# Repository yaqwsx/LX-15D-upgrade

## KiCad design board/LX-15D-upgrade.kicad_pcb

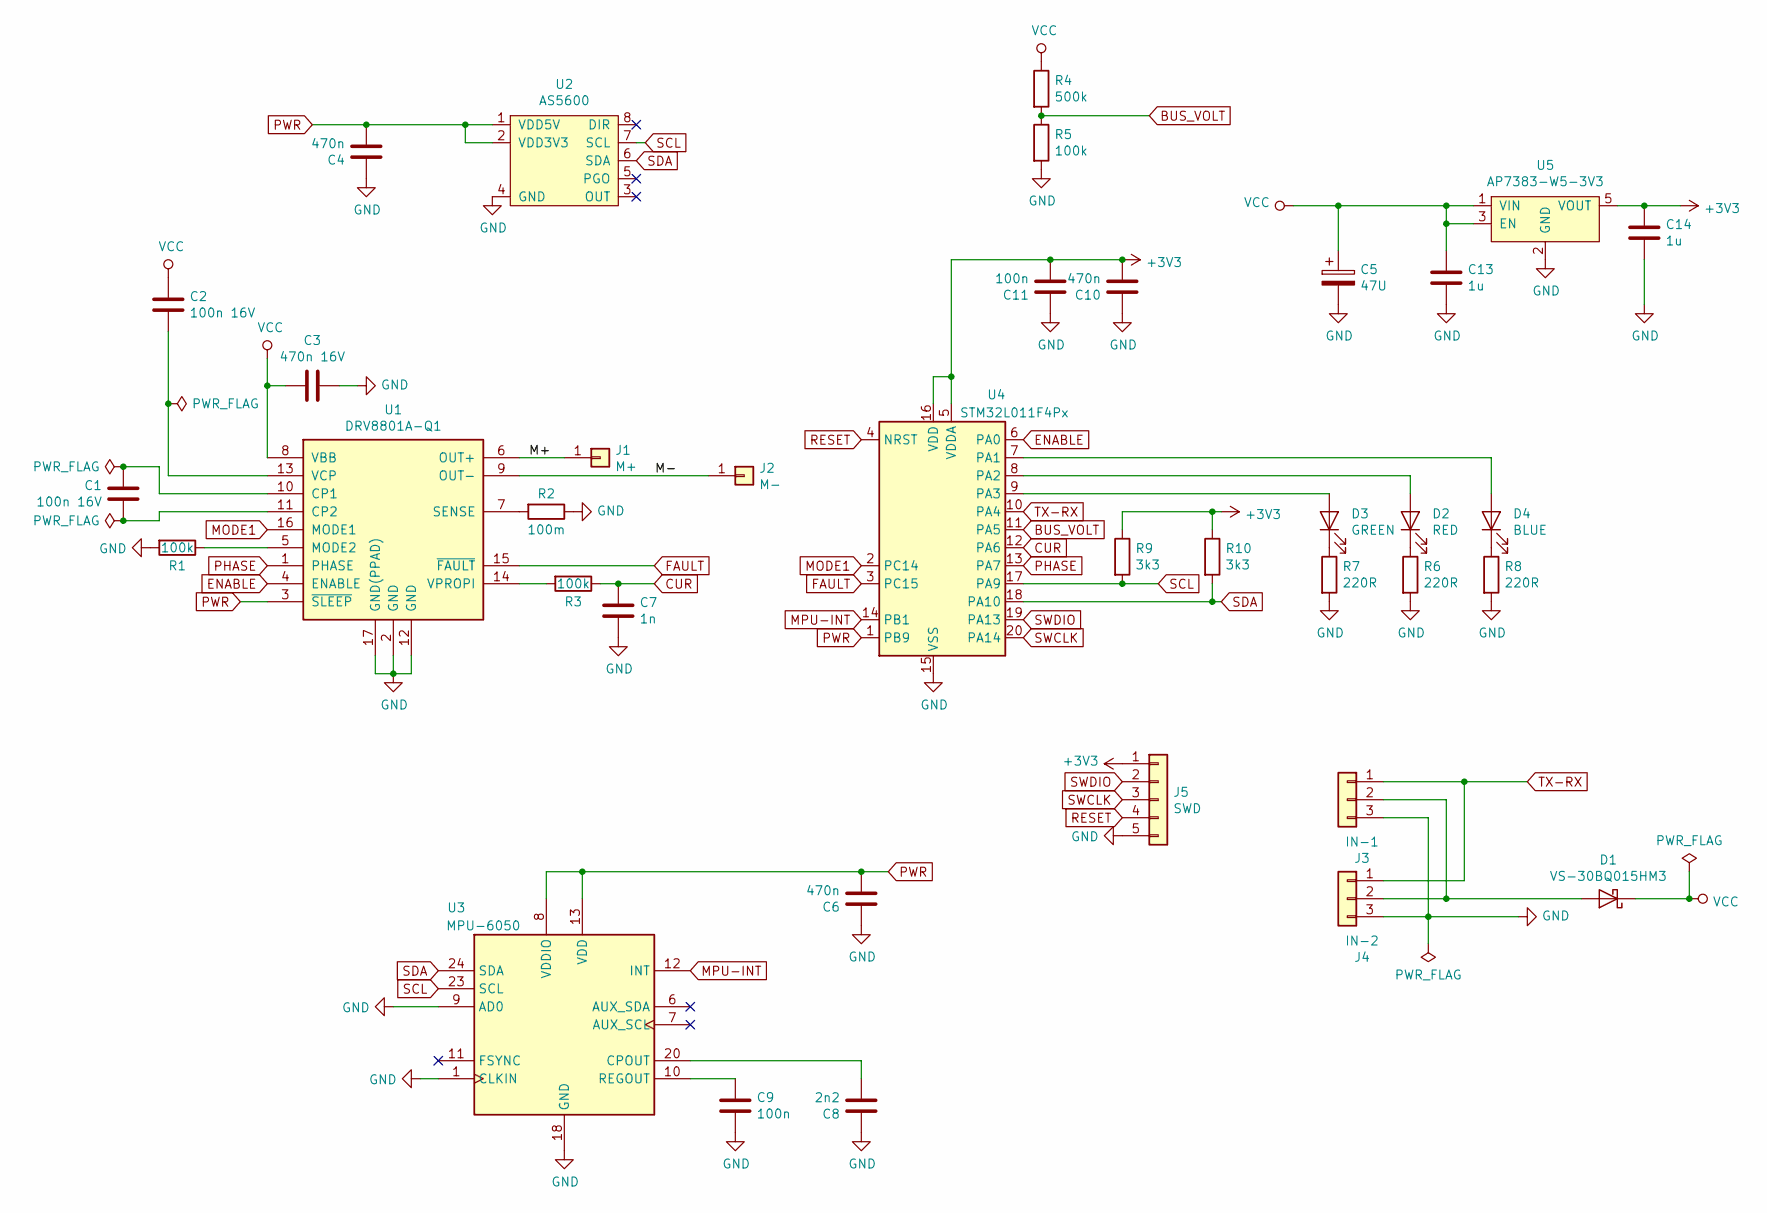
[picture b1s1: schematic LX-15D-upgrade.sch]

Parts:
C1, C2: 100n 16V; C_0603_1608Metric_Pad1.05x0.95mm_HandSolder
C3: 470n 16V; C_0603_1608Metric_Pad1.05x0.95mm_HandSolder
C4, C6, C10: 470n; C_0603_1608Metric_Pad1.05x0.95mm_HandSolder
C5: 47U; CP_EIA-6032-28_Kemet-C; mfr# TAJC476K016SNJ
C7: 1n; C_0603_1608Metric_Pad1.05x0.95mm_HandSolder
C8: 2n2; C_0603_1608Metric_Pad1.05x0.95mm_HandSolder
C9, C11: 100n; C_0603_1608Metric_Pad1.05x0.95mm_HandSolder
C13, C14: 1u; C_0603_1608Metric_Pad1.05x0.95mm_HandSolder
D1: VS-30BQ015HM3; D_2512_6332Metric
D2: RED; LED_0603_1608Metric
D3: GREEN; LED_0603_1608Metric
D4: BLUE; LED_0603_1608Metric
J1: M+; Pin_D1.0mm_L10.0mm
J2: M-; Pin_D1.0mm_L10.0mm
J3: IN-1; Molex_Micro-Latch_53253-0370_1x03_P2.00mm_Vertical
J4: IN-2; Molex_Micro-Latch_53253-0370_1x03_P2.00mm_Vertical
J5: SWD; PinHeader_1x05_P2.00mm_Vertical
R1, R3, R5: 100k; R_0603_1608Metric_Pad1.05x0.95mm_HandSolder
R2: 100m; R_2512_6332Metric_Pad1.52x3.35mm_HandSolder
R4: 500k; R_0603_1608Metric_Pad1.05x0.95mm_HandSolder
R6, R7, R8: 220R; R_0603_1608Metric_Pad1.05x0.95mm_HandSolder
R9, R10: 3k3; R_0603_1608Metric_Pad1.05x0.95mm_HandSolder
U1: DRV8801A-Q1; Texas_S-PWQFN-N16_EP2.1x2.1mm_ThermalVias
U2: AS5600; SOIC-8_3.9x4.9mm_P1.27mm
U3: MPU-6050; InvenSense_QFN-24_4x4mm_P0.5mm
U4: STM32L011F4Px; TSSOP-20_4.4x6.5mm_P0.65mm
U5: AP7383-W5-3V3; SOT-23-5

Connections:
+3V3: C10.2, C11.2, C14.1, J5.1, R9.1, R10.1, U4.5 (VDDA), U4.16 (VDD), U5.5 (VOUT)
/M+: J1.1, U1.6 (OUT+)
/M-: J2.1, U1.9 (OUT-)
BUS_VOLT: R4.2, R5.1, U4.11 (PA5)
CUR: C7.1, R3.1, U4.12 (PA6)
ENABLE: U1.4 (ENABLE), U4.6 (PA0)
FAULT: U1.15 (~FAULT), U4.3 (PC15)
GND: C3.1, C4.1, C5.2, C6.1, C7.2, C8.1, C9.2, C10.1, C11.1, C13.2, C14.2, J3.3, J4.3, J5.5, R1.2, R2.1, R5.2, R6.2, R7.2, R8.2, U1.2 (GND), U1.12 (GND), U1.17 (GND(PPAD)), U2.4 (GND), U3.1 (CLKIN), U3.9 (AD0), U3.18 (GND), U4.15 (VSS), U5.2 (GND)
MODE1: U1.16 (MODE1), U4.2 (PC14)
MPU-INT: U3.12 (INT), U4.14 (PB1)
unnamed: C1.1, U1.11 (CP2)
unnamed: C1.2, U1.10 (CP1)
unnamed: C2.2, U1.13 (VCP)
unnamed: C8.2, U3.20 (CPOUT)
unnamed: C9.1, U3.10 (REGOUT)
unnamed: D1.2 (A), J3.2, J4.2
unnamed: D2.1 (K), R6.1
unnamed: D2.2 (A), U4.8 (PA2)
unnamed: D3.1 (K), R7.1
unnamed: D3.2 (A), U4.9 (PA3)
unnamed: D4.1 (K), R8.1
unnamed: D4.2 (A), U4.7 (PA1)
unnamed: R1.1, U1.5 (MODE2)
unnamed: R2.2, U1.7 (SENSE)
unnamed: R3.2, U1.14 (VPROPI)
PHASE: U1.1 (PHASE), U4.13 (PA7)
PWR: C4.2, C6.2, U1.3 (~SLEEP), U2.1 (VDD5V), U2.2 (VDD3V3), U3.8 (VDDIO), U3.13 (VDD), U4.1 (PB9)
RESET: J5.4, U4.4 (NRST)
SCL: R9.2, U2.7 (SCL), U3.23 (SCL), U4.17 (PA9)
SDA: R10.2, U2.6 (SDA), U3.24 (SDA), U4.18 (PA10)
SWCLK: J5.3, U4.20 (PA14)
SWDIO: J5.2, U4.19 (PA13)
TX-RX: J3.1, J4.1, U4.10 (PA4)
VCC: C2.1, C3.2, C5.1, C13.1, D1.1 (K), R4.1, U1.8 (VBB), U5.1 (VIN), U5.3 (EN)

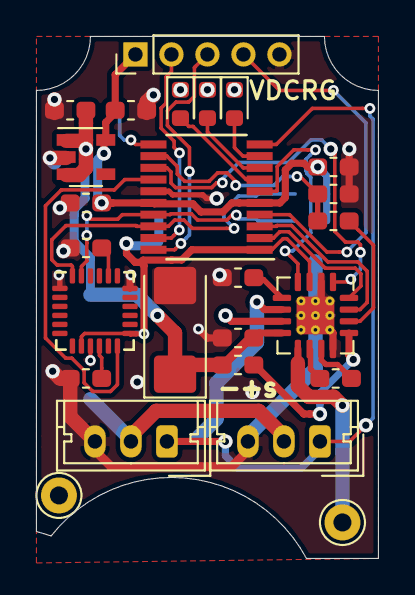
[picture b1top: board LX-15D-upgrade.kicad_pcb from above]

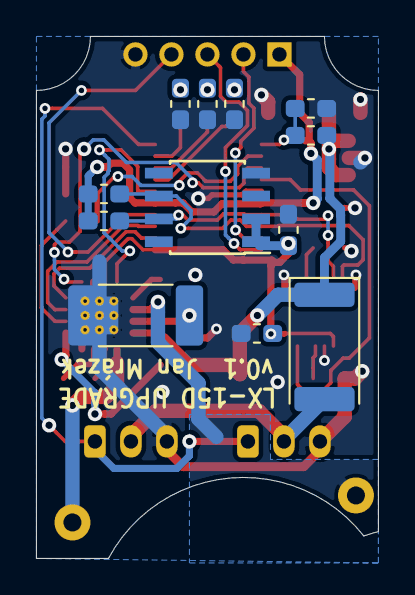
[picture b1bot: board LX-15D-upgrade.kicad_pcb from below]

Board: 2 copper layers, 19.0 x 29.0 mm, 37 parts (12 on the bottom side), 34 nets.

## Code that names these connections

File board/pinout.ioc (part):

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Mcu.Name=STM32L011F(3-4)Px
Mcu.Package=TSSOP20
Mcu.UserName=STM32L011F4Px
PA0-CK_IN.Signal=S_TIM2_CH1
PA1.Signal=S_TIM2_CH2
PA10.Mode=I2C
PA10.Signal=I2C1_SDA
PA13.Mode=Serial_Wire
PA13.Signal=SYS_SWDIO
PA14.Mode=Serial_Wire
PA14.Signal=SYS_SWCLK
PA2.Signal=S_TIM2_CH3
PA3.Signal=S_TIM2_CH4
PA4.Mode=Half_duplex(single_wire_mode)
PA4.Signal=LPUART1_TX
PA5.Signal=GPIO_Analog
PA6.Signal=GPIO_Analog
PA7.Signal=GPIO_Output
PA9.Mode=I2C
PA9.Signal=I2C1_SCL
PB1.Signal=GPXTI1
PB9-BOOT0.Signal=GPXTI9
PC14-OSC32_IN.Signal=GPIO_Output
PC15-OSC32_OUT.Signal=GPIO_Output
RCC.HSE_VALUE=8000000
RCC.SYSCLKFreq_VALUE=2097000
board=custom

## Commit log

2019-04-03 Initial board schematics
2019-04-04 Route v0.1
2019-04-08 Add power decoupling capacitor
2019-04-12 Add makefile for exporting gerbers
2019-04-12 Final tweak
2019-04-12 Build panel for manufacturing
